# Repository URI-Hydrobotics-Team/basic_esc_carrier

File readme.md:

# Blue Robotics Basic ESC 3x Carrier Board
A very simple, stackable, board that provides mounting and power/signal connections for three Blue Robotics Basic ESCs. This board will not implement any kind of load switching for kill switch functionality.

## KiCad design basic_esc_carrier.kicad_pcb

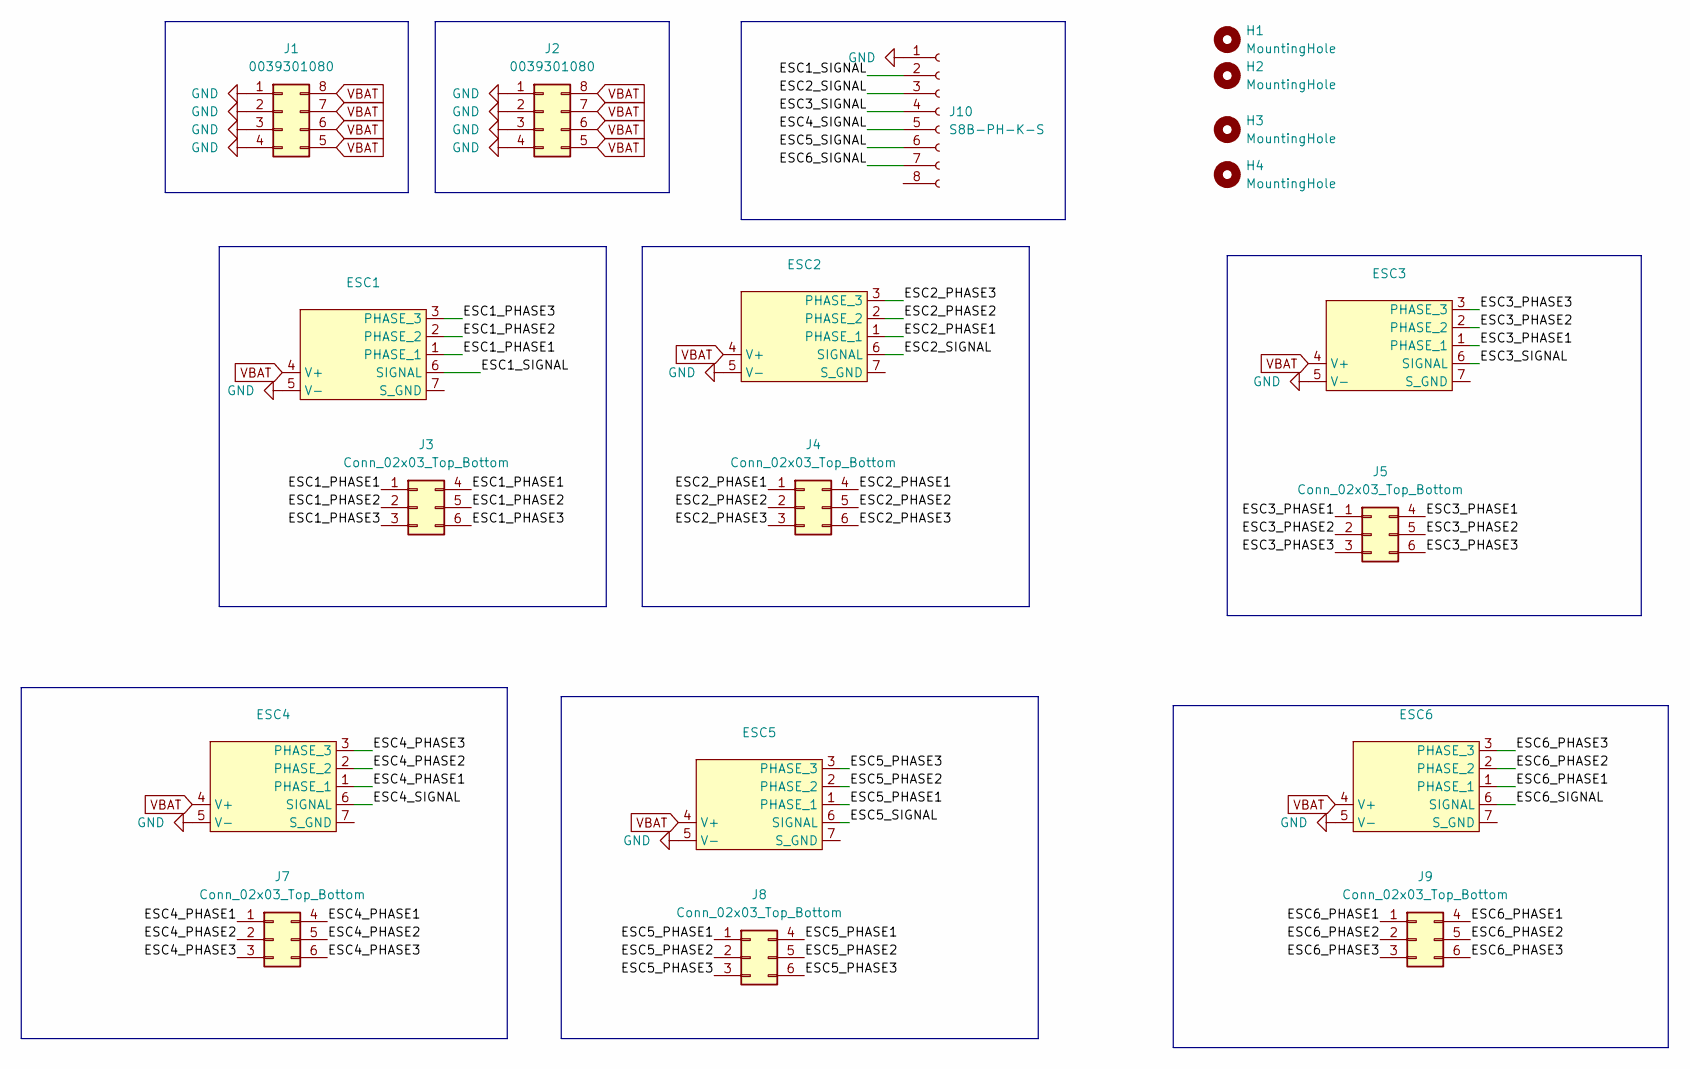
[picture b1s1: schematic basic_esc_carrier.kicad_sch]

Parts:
ESC1, ESC2, ESC3, ESC4, ESC5, ESC6: basic_esc
H1, H2, H3, H4: MountingHole; MountingHole_3.2mm_M3
J1, J2: 0039301080; Molex_Mini-Fit_Jr_5569-08A2_2x04_P4.20mm_Horizontal
J3, J4, J5, J7, J8, J9: Conn_02x03_Top_Bottom; Molex_Mini-Fit_Jr_5569-06A2_2x03_P4.20mm_Horizontal
J10: S8B-PH-K-S; JST_PH_S8B-PH-K_1x08_P2.00mm_Horizontal

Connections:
/ESC1_PHASE1: ESC1.1 (PHASE_1), J3.1, J3.4
/ESC1_PHASE2: ESC1.2 (PHASE_2), J3.2, J3.5
/ESC1_PHASE3: ESC1.3 (PHASE_3), J3.3, J3.6
/ESC1_SIGNAL: ESC1.6 (SIGNAL), J10.2
/ESC2_PHASE1: ESC2.1 (PHASE_1), J4.1, J4.4
/ESC2_PHASE2: ESC2.2 (PHASE_2), J4.2, J4.5
/ESC2_PHASE3: ESC2.3 (PHASE_3), J4.3, J4.6
/ESC2_SIGNAL: ESC2.6 (SIGNAL), J10.3
/ESC3_PHASE1: ESC3.1 (PHASE_1), J5.1, J5.4
/ESC3_PHASE2: ESC3.2 (PHASE_2), J5.2, J5.5
/ESC3_PHASE3: ESC3.3 (PHASE_3), J5.3, J5.6
/ESC3_SIGNAL: ESC3.6 (SIGNAL), J10.4
/ESC4_PHASE1: ESC4.1 (PHASE_1), J7.1, J7.4
/ESC4_PHASE2: ESC4.2 (PHASE_2), J7.2, J7.5
/ESC4_PHASE3: ESC4.3 (PHASE_3), J7.3, J7.6
/ESC4_SIGNAL: ESC4.6 (SIGNAL), J10.5
/ESC5_PHASE1: ESC5.1 (PHASE_1), J8.1, J8.4
/ESC5_PHASE2: ESC5.2 (PHASE_2), J8.2, J8.5
/ESC5_PHASE3: ESC5.3 (PHASE_3), J8.3, J8.6
/ESC5_SIGNAL: ESC5.6 (SIGNAL), J10.6
/ESC6_PHASE1: ESC6.1 (PHASE_1), J9.1, J9.4
/ESC6_PHASE2: ESC6.2 (PHASE_2), J9.2, J9.5
/ESC6_PHASE3: ESC6.3 (PHASE_3), J9.3, J9.6
/ESC6_SIGNAL: ESC6.6 (SIGNAL), J10.7
GND: ESC1.5 (V-), ESC2.5 (V-), ESC3.5 (V-), ESC4.5 (V-), ESC5.5 (V-), ESC6.5 (V-), J1.1, J1.2, J1.3, J1.4, J2.1, J2.2, J2.3, J2.4, J10.1
VBAT: ESC1.4 (V+), ESC2.4 (V+), ESC3.4 (V+), ESC4.4 (V+), ESC5.4 (V+), ESC6.4 (V+), J1.5, J1.6, J1.7, J1.8, J2.5, J2.6, J2.7, J2.8

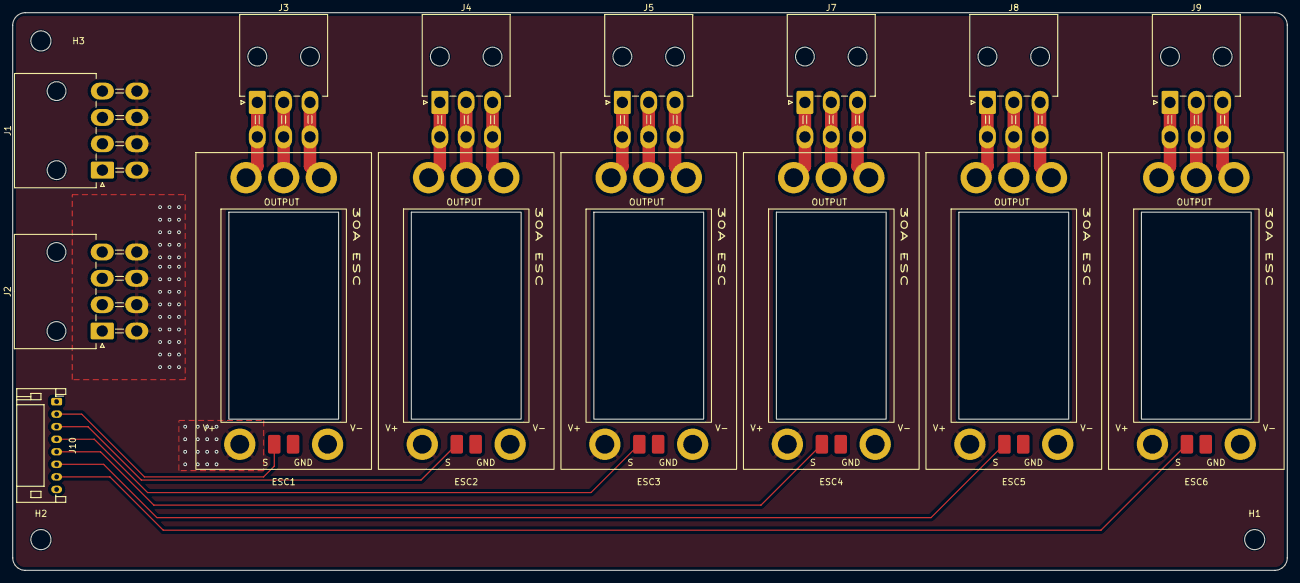
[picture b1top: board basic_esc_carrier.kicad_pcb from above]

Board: 2 copper layers, 203.2 x 88.9 mm, 19 parts (0 on the bottom side), 26 nets.
